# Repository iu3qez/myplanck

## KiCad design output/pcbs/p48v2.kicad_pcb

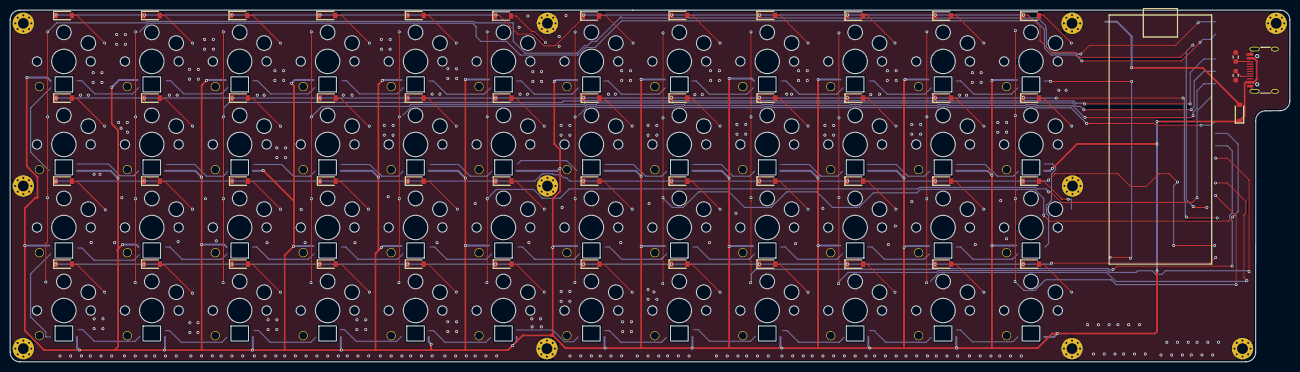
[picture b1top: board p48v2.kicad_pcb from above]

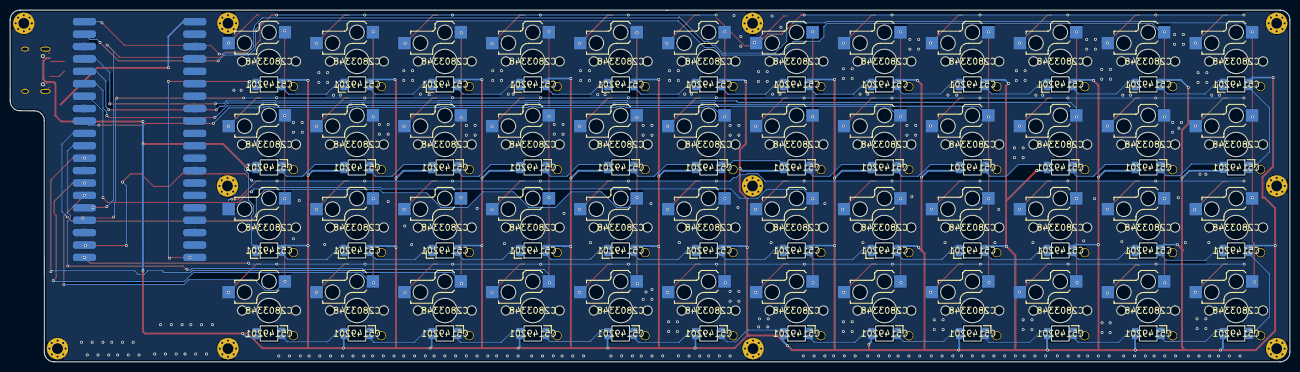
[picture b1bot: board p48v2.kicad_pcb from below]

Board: 2 copper layers, 262.0 x 72.0 mm, 160 parts (96 on the bottom side), 117 nets.

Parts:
19.051: pico
D1, D2, D3, D4, D5, D6, D7, D8, D9, D10, D11, D12, D13, D14, D15, D16, D17, D18, D19, D20, D21, D22, D23, D24, D25, D26, D27, D28, D29, D30, D31, D32, D33, D34, D35, D36, D37, D38, D39, D40, D41, D42, D43, D44, D45, D46, D47, D48, D49: diode_tht_sod123
H1, H2, H3, H4, H5, H6, H7, H8, H9, H10, H11: mountingholem2
J1: usb_c_hro_type_c_31_m_12
LED1, LED2, LED3, LED4, LED5, LED6, LED7, LED8, LED9, LED10, LED11, LED12, LED13, LED14, LED15, LED16, LED17, LED18, LED19, LED20, LED21, LED22, LED23, LED24, LED25, LED26, LED27, LED28, LED29, LED30, LED31, LED32, LED33, LED34, LED35, LED36, LED37, LED38, LED39, LED40, LED41, LED42, LED43, LED44, LED45, LED46, LED47, LED48: led_SK6812mini-e (per-keysingle-side)
R1, R2: resistor_0603
S1, S2, S3, S4, S5, S6, S7, S8, S9, S10, S11, S12, S13, S14, S15, S16, S17, S18, S19, S20, S21, S22, S23, S24, S25, S26, S27, S28, S29, S30, S31, S32, S33, S34, S35, S36, S37, S38, S39, S40, S41, S42, S43, S44, S45, S46, S47, S48: switch_choc_v1_v2

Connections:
COL0: 19.051.1, S1.1, S2.1, S3.1, S4.1
COL1: 19.051.2, S5.1, S6.1, S7.1, S8.1
COL2: 19.051.4, S9.1, S10.1, S11.1, S12.1
COL3: 19.051.5, S13.1, S14.1, S15.1, S16.1
COL4: 19.051.6, S17.1, S18.1, S19.1, S20.1
COL5: 19.051.7, S21.1, S22.1, S23.1, S24.1
COL6: 19.051.9, S25.1, S26.1, S27.1, S28.1
COL7: 19.051.10, S29.1, S30.1, S31.1, S32.1
COL8: 19.051.11, S33.1, S34.1, S35.1, S36.1
COL9: 19.051.12, S37.1, S38.1, S39.1, S40.1
COL10: 19.051.14, S41.1, S42.1, S43.1, S44.1
COL11: 19.051.15, S45.1, S46.1, S47.1, S48.1
CR_0_0: D4.2, S4.2
CR_0_1: D3.2, S3.2
CR_0_2: D2.2, S2.2
CR_0_3: D1.2, S1.2
CR_1_0: D8.2, S8.2
CR_1_1: D7.2, S7.2
CR_1_2: D6.2, S6.2
CR_1_3: D5.2, S5.2
CR_2_0: D12.2, S12.2
CR_2_1: D11.2, S11.2
CR_2_2: D10.2, S10.2
CR_2_3: D9.2, S9.2
CR_3_0: D16.2, S16.2
CR_3_1: D15.2, S15.2
CR_3_2: D14.2, S14.2
CR_3_3: D13.2, S13.2
CR_4_0: D20.2, S20.2
CR_4_1: D19.2, S19.2
CR_4_2: D18.2, S18.2
CR_4_3: D17.2, S17.2
CR_5_0: D24.2, S24.2
CR_5_1: D23.2, S23.2
CR_5_2: D22.2, S22.2
CR_5_3: D21.2, S21.2
CR_6_0: D28.2, S28.2
CR_6_1: D27.2, S27.2
CR_6_2: D26.2, S26.2
CR_6_3: D25.2, S25.2
CR_7_0: D32.2, S32.2
CR_7_1: D31.2, S31.2
CR_7_2: D30.2, S30.2
CR_7_3: D29.2, S29.2
CR_8_0: D36.2, S36.2
CR_8_1: D35.2, S35.2
CR_8_2: D34.2, S34.2
CR_8_3: D33.2, S33.2
CR_9_0: D40.2, S40.2
CR_9_1: D39.2, S39.2
CR_9_2: D38.2, S38.2
CR_9_3: D37.2, S37.2
CR_10_0: D44.2, S44.2
CR_10_1: D43.2, S43.2
CR_10_2: D42.2, S42.2
CR_10_3: D41.2, S41.2
CR_11_0: D48.2, S48.2
CR_11_1: D47.2, S47.2
CR_11_2: D46.2, S46.2
CR_11_3: D45.2, S45.2
GND: 19.051.3, 19.051.8, 19.051.13, 19.051.18, 19.051.23, 19.051.28, 19.051.33, 19.051.38, H1.1, H2.1, H3.1, H4.1, H5.1, H6.1, H7.1, H8.1, H9.1, H10.1, H11.1, J1.A1, J1.A12, J1.B1, J1.B12, J1.S1, LED1.3, LED2.3, LED3.3, LED4.3, LED5.3, LED6.3, LED7.3, LED8.3, LED9.3, LED10.3, LED11.3, LED12.3, LED13.3, LED14.3, LED15.3, LED16.3, LED17.3, LED18.3, LED19.3, LED20.3, LED21.3, LED22.3, LED23.3, LED24.3, LED25.3, LED26.3, LED27.3, LED28.3, LED29.3, LED30.3, LED31.3, LED32.3, LED33.3, LED34.3, LED35.3, LED36.3, LED37.3, LED38.3, LED39.3, LED40.3, LED41.3, LED42.3, LED43.3, LED44.3, LED45.3, LED46.3, LED47.3, LED48.3, R1.2, R2.2
LED0: 19.051.21, LED48.4
LED1: LED44.4, LED48.2
LED2: LED40.4, LED44.2
LED3: LED36.4, LED40.2
LED4: LED32.4, LED36.2
LED5: LED28.4, LED32.2
LED6: LED24.4, LED28.2
LED7: LED20.4, LED24.2
LED8: LED16.4, LED20.2
LED9: LED12.4, LED16.2
LED10: LED8.4, LED12.2
LED11: LED4.4, LED8.2
LED12: LED3.4, LED4.2
LED13: LED3.2, LED7.4
LED14: LED7.2, LED11.4
LED15: LED11.2, LED15.4
LED16: LED15.2, LED19.4
LED17: LED19.2, LED23.4
LED18: LED23.2, LED27.4
LED19: LED27.2, LED31.4
LED20: LED31.2, LED35.4
LED21: LED35.2, LED39.4
LED22: LED39.2, LED43.4
LED23: LED43.2, LED47.4
LED24: LED46.4, LED47.2
LED25: LED42.4, LED46.2
LED26: LED38.4, LED42.2
LED27: LED34.4, LED38.2
LED28: LED30.4, LED34.2
LED29: LED26.4, LED30.2
LED30: LED22.4, LED26.2
LED31: LED18.4, LED22.2
LED32: LED14.4, LED18.2
LED33: LED10.4, LED14.2
LED34: LED6.4, LED10.2
LED35: LED2.4, LED6.2
LED36: LED1.4, LED2.2
LED37: LED1.2, LED5.4
LED38: LED5.2, LED9.4
LED39: LED9.2, LED13.4
LED40: LED13.2, LED17.4
LED41: LED17.2, LED21.4
LED42: LED21.2, LED25.4
LED43: LED25.2, LED29.4
LED44: LED29.2, LED33.4
LED45: LED33.2, LED37.4
LED46: LED37.2, LED41.4
LED47: LED41.2, LED45.4
ROW0: 19.051.16, D4.1, D8.1, D12.1, D16.1, D20.1, D24.1, D28.1, D32.1, D36.1, D40.1, D44.1, D48.1
ROW1: 19.051.17, D3.1, D7.1, D11.1, D15.1, D19.1, D23.1, D27.1, D31.1, D35.1, D39.1, D43.1, D47.1
ROW2: 19.051.19, D2.1, D6.1, D10.1, D14.1, D18.1, D22.1, D26.1, D30.1, D34.1, D38.1, D42.1, D46.1
ROW3: 19.051.20, D1.1, D5.1, D9.1, D13.1, D17.1, D21.1, D25.1, D29.1, D33.1, D37.1, D41.1, D45.1
USB2_CC1: J1.A5, R1.1
USB2_CC2: J1.B5, R2.1
VBUS: 19.051.40, D49.2
VCC: D49.1, J1.A4, J1.A9, J1.B4, J1.B9, LED1.1, LED2.1, LED3.1, LED4.1, LED5.1, LED6.1, LED7.1, LED8.1, LED9.1, LED10.1, LED11.1, LED12.1, LED13.1, LED14.1, LED15.1, LED16.1, LED17.1, LED18.1, LED19.1, LED20.1, LED21.1, LED22.1, LED23.1, LED24.1, LED25.1, LED26.1, LED27.1, LED28.1, LED29.1, LED30.1, LED31.1, LED32.1, LED33.1, LED34.1, LED35.1, LED36.1, LED37.1, LED38.1, LED39.1, LED40.1, LED41.1, LED42.1, LED43.1, LED44.1, LED45.1, LED46.1, LED47.1, LED48.1

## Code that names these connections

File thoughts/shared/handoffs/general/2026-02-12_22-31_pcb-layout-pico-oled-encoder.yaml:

---
session: general
date: 2026-02-12
status: partial
outcome: PARTIAL_PLUS
---

goal: Create KiCad project for 4x12 Planck keyboard with Pico 2, OLED, encoder
now: Place Pico SMD (B.Cu), OLED 1.3" (F.Cu rotated 90), encoder (F.Cu) in right extension - USE PCBNEW NOT manual file edits

test: "Open /home/sf/src/myplanck/output/pcbs/p48v2.kicad_pcb in pcbnew - verify clean board with 48 switches/LEDs/diodes"

done_this_session:
  - task: Fixed ergogen config - renamed to folder mode, downloaded ceoloide footprints
    files: [config.yaml, footprints/ceoloide/switch_choc_v1_v2.js, footprints/ceoloide/led_sk6812mini-e.js, footprints/ceoloide/diode_tht_sod123.js]
  - task: Rewrote config from direct-pin to 4x12 matrix with diodes
    files: [config.yaml]
  - task: Fixed outline from 418x123mm (wrong) to 220x72mm (correct size for Planck)
    files: [config.yaml]
  - task: Installed KiCad libraries and configured sym-lib-table/fp-lib-table
    files: [~/.config/kicad/9.0/sym-lib-table, ~/.config/kicad/9.0/fp-lib-table]
  - task: Identified component placement strategy - right side extension for Pico/OLED/encoder
    files: []
  - task: Documented KiCad MCP server bugs
    files: [/home/sf/src/KiCAD-MCP-Server/bug.md]

blockers:
  - KiCad MCP place_component breaks after delete cycles (FootprintLoad swig error)
  - MCP search_footprints returns "undefined" for all results
  - Manual PCB file editing causes layer corruption on footprints - DO NOT DO THIS

questions:
  - Should the board outline extension be done in ergogen config.yaml or modified in pcbnew?
  - Exact Pico position in extension to avoid switch through-hole interference

decisions:
  - matrix_with_diodes: 4x12 matrix (16 GPIO) instead of direct-pin (48 GPIO) - allows Pico 2 which has 30 GPIO
  - pico_smd: Use Module:RaspberryPi_Pico_Common_SMD (castellated) not THT - THT holes interfere with switch holes
  - dual_side_layout: Pico on B.Cu, OLED on F.Cu - allows overlap, minimizes extension width
  - right_extension: 30mm extension on right side for Pico+OLED+encoder, board 250x72mm total
  - led_vbus: LED VCC direct from VBUS 5V (bypasses 3.3V regulator, handles 2.88A max)
  - oled_rotated: OLED 1.3" should be rotated 90 degrees to fit in narrow extension

findings:
  - ergogen_outline_bug: "size: [12kx+4, 4ky+4]" creates 220x72 rect per KEY then takes bounding box = 418x123mm. Correct is "size: [kx+4, ky+4]"
  - pico_smd_origin: SMD footprint origin is at CENTER (not pad 1). Pads at x=+/-9.69, y=-24.13 to +24.13
  - switch_holes: Each switch has 5 through-holes (center 5mm, 2x alignment 1.9mm, stabilizer 1.6mm, boss 3mm)
  - zero_conflict_zone: Pico fits horizontally at y<-106 or vertically at y<-140 with 0 switch hole conflicts
  - mcp_footprint_cache: MCP caches library paths at startup - must restart to pick up newly installed libs

worked:
  - Ergogen folder mode with ceoloide footprints works perfectly
  - MCP place_component works for initial placement (before delete cycles)
  - MCP open_project/save_project/find_component/move_component all work reliably
  - Board outline calculation from switch positions

failed:
  - Manual footprint insertion into PCB file - layer handling is complex, causes corruption
  - MCP place_component after delete+re-place cycles - swig FootprintLoad error
  - MCP search_footprints/list_library_footprints - always returns undefined
  - Placing Pico over switch area - even SMD body blocks through-holes physically

next:
  - Regenerate clean PCB with ergogen (just run npx ergogen . -o output --clean)
  - Extend board outline to 250x72mm - either via ergogen config or pcbnew Edit > Board Setup
  - Place components IN PCBNEW (not via file edits) - Pico SMD on B.Cu, OLED rotated 90 on F.Cu, EC11 on F.Cu
  - Add nets for new components (LED_DATA, VBUS, I2C SDA/SCL, ENC_A/B/SW)
  - Assign nets to Pico pins (COL0-11=GP0-11, ROW0-3=GP12-15, LED_DATA=GP16, I2C=GP20-21, ENC=GP17-19)
  - Create schematic (.kicad_sch)
  - Route traces
  - Run DRC
  - Add bypass capacitors for LED power

files:
  created:
    - footprints/ceoloide/switch_choc_v1_v2.js
    - footprints/ceoloide/led_sk6812mini-e.js
    - footprints/ceoloide/diode_tht_sod123.js
    - /home/sf/src/KiCAD-MCP-Server/bug.md
  modified:
    - config.yaml (renamed from ergogen.yaml, rewritten for matrix+diodes, fixed outline)
    - output/pcbs/p48v2.kicad_pcb (regenerated multiple times)
    - ~/.config/kicad/9.0/sym-lib-table
    - ~/.config/kicad/9.0/fp-lib-table

pin_mapping:
  COL0-COL11: GPIO0-GPIO11 (Pico pads 1,2,4,5,6,7,9,10,11,12,14,15)
  ROW0-ROW3: GPIO12-GPIO15 (Pico pads 16,17,19,20)
  LED_DATA: GPIO16 (Pico pad 21)
  ENC_A: GPIO17 (Pico pad 22)
  ENC_B: GPIO18 (Pico pad 24)
  ENC_SW: GPIO19 (Pico pad 25)
  I2C_SDA: GPIO20 (Pico pad 26)
  I2C_SCL: GPIO21 (Pico pad 27)
  VBUS_LED: VBUS (Pico pad 40)
  GND: pads 3,8,13,18,23,28,33,38

kicad_footprints:
  pico: "Module:RaspberryPi_Pico_Common_SMD"
  oled: "Display:Adafruit_SSD1306_No_Mounting_Holes"
  encoder: "Rotary_Encoder:RotaryEncoder_Alps_EC11E-Switch_Vertical_H20mm"

kicad_symbols:
  pico: "MCU_Module:RaspberryPi_Pico"

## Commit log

2026-03-02 Initial commit: Planck 4x12 custom keyboard PCB
    Ergogen config for 4x12 ortholinear matrix with Choc v1/v2 hotswap,
    per-key SK6812mini-e RGB LEDs, Raspberry Pi Pico 2, SSD1306 OLED,
    EC11 rotary encoder. Includes KiCad PCB with manual edits
    (component placement, net assignments, GND zones).
2026-03-02 Add design doc: replace OLED breakout with bare 1.3" SSD1306 FPC panel
    Adafruit module PCB protrudes too much for low-profile Choc switches.
    Bare panel (1.45mm) + FPC ZIF connector + ~9 passives on PCB instead.
2026-03-02 Add implementation plan: OLED bare panel FPC integration
    6 tasks: remove U2, add nets, place FPC connector + passives,
    verify layout, update docs.
2026-03-03 Remove Adafruit SSD1306 module (U2) from PCB
2026-03-03 Add OLED internal nets for FPC bare panel circuit
2026-03-03 Place FPC connector J1 and OLED passives (C1-C6, R1-R3) on F.Cu
    J1: Hirose FH12-30S-0.5SH 30-pin FPC ZIF at (333, -19)
    - All 30 pins + 2 MP pads with net assignments for I2C mode
    - BS0/BS1/BS2=GND (I2C), D/C=GND (addr 0x3C)
    - D0=I2C_SCL, D1+D2=I2C_SDA
    Passives clustered around J1:
    - C1,C2: 1uF charge pump caps (C1P/C1N, C2P/C2N)
2026-03-03 Update docs: OLED changed from breakout module to bare FPC panel
    - Replace U2 entry with J1 FPC connector + C1-C6/R1-R3 passives
    - Add newly discovered MCP limitations (find_component freeze,
    add_net not persisting, export_svg silent failure)
    - Add no co-author commit rule
2026-03-03 Add USB-C power input for LED 5V (J2, R4, R5, D49)
    J2: HRO TYPE-C-31-M-12 (C165948) power-only USB-C connector
    R4, R5: 5.1k CC1/CC2 pulldowns for USB-C negotiation
    D49: B5819W Schottky for backfeed protection on Pico VBUS
    Circuit: external 5V via J2 feeds VCC (LED rail) directly,
    Pico VBUS feeds VCC through Schottky D49 to prevent backfeed.
    Components at temporary position, to be moved in pcbnew.
2026-03-03 Rebuild board outline with USB-C extension and filleted corners
    Extension tab (332→343, -87→-97.5) below main board for USB-C
    power connector J2. All 6 corners with r=2 fillet including
    concave inner corner at (332,-87) near Pico pin 1.
2026-03-03 Add project memory files for cross-machine sessions
2026-03-04 Fix diode-hotswap interference, add Pico and mounting holes to ergogen
    - Move diodes from B.Cu to F.Cu, shift from [0,-8.5] to [0,9.5] (above switch)
    - Rewrite diode footprint with standard SOD-123 fab outline and courtyard
    - Add Pico THT footprint (from AlexSutila/ergogen-footprints, KiCad 8)
    - Add M2 mounting hole footprints (hole + mounting with via ring)
    - Add Pico to config with full net mapping (COL0-11, ROW0-3, LED, encoder, I2C)
    - Add 11 M2 mounting holes (4 corners, 3 mid-edge, 2 center, 2 extension)
2026-03-06 Add USB-C power footprint, 0603 resistor, and Pico castellated option
    New ergogen footprints:
    - usb_c_hro_type_c_31_m_12.js: HRO TYPE-C-31-M-12 USB-C receptacle
    - resistor_0603.js: 0603 HandSolder SMD resistor
    Pico footprint now supports castellated mounting (SMD pads at board edge)
    via castellated: true param. Config updated to use castellated on B.Cu.
    Config additions: J2 (USB-C power), R4/R5 (CC pulldowns), D49 (Schottky)
2026-03-06 Enlarge Pico castellated pads, add Power netclass 1.0mm track
    Pico castellated pads: 4.8x1.6mm at board edge with 50% more exposed area.
    Power netclass: 1.0mm track, 0.3mm clearance, 0.8/0.4mm via.
    Assigned VCC, VBUS, GND, VSYS, OUT_3V3, VCC_3V3 to Power class.
2026-03-06 Manual KiCad edits: routing and board setup
2026-03-08 feat: reorder LED chain to zigzag pattern with row-specific rotation
    - Change from serpentine to top-right descending zigzag
    - Alternate rotation per row for proper zig-zag spacing
    - Add LCSC C5149201 part number to all SK6812mini-e LEDs
    - Split LED footprint config by row for rotation control
2026-03-09 Save PCB state (locked - no more ergogen regeneration)
